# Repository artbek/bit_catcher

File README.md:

Bit Catcher (Mini Game Console)
===============================

Video: https://youtu.be/HpCyLKLNJE4

<br />

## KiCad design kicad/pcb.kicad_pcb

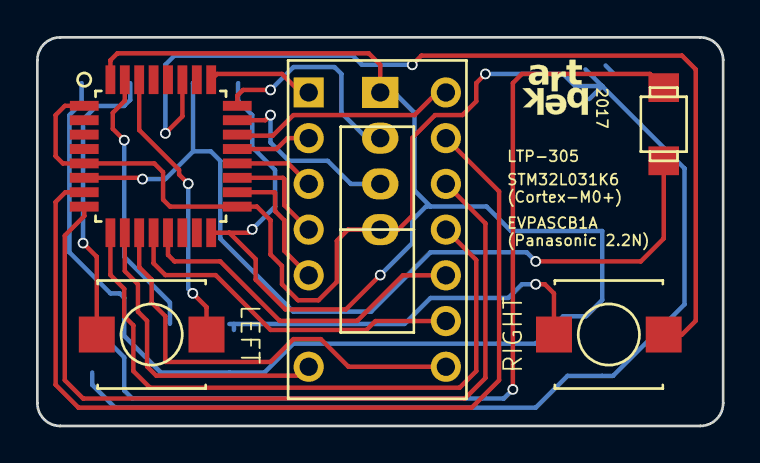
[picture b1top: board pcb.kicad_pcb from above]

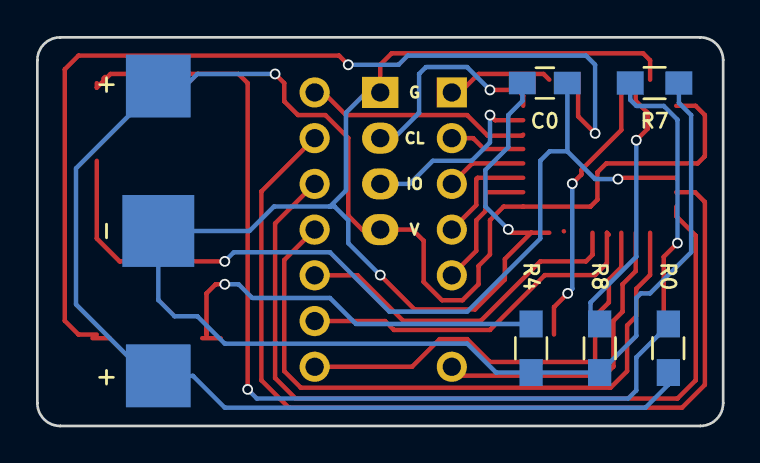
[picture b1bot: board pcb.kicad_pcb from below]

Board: 2 copper layers, 38.1 x 21.6 mm, 12 parts (6 on the bottom side), 24 nets.

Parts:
BT0: Battery_Cell; BatteryHolder_1220
BTN4: RIGHT; SW_PANASONIC
BTN7: LEFT; SW_PANASONIC
C0: 100nF; C_0805_HandSoldering
J0: Conn_01x04; SWD_PROGRAMMING_HEADER
R0, R4, R7, R8: 2k; R_0805_HandSoldering
S0: 5x7_DISPLAY_LTP-305; 2x7_dot_matrix
SW0: ON_OFF; SW_OMRON_SMALL
U0: STM32L031x4/6; TQFP-32_7x7mm_Pitch0.8mm

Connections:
+3V3: BT0.1, J0.4, R0.1, U0.1, U0.5, U0.17
GND: BT0.2, C0.2, J0.1, R4.1, R7.1, R8.1, U0.16, U0.32
unnamed: C0.1, SW0.1, U0.6
unnamed: J0.2, U0.24
unnamed: J0.3, U0.23
unnamed: R0.2, SW0.2
unnamed: BTN4.1, R4.2
unnamed: BTN7.2, R7.2
unnamed: R8.2, U0.31
unnamed: S0.1C, U0.25
unnamed: S0.2, U0.21
unnamed: S0.3, U0.20
unnamed: S0.4, U0.19
unnamed: S0.5C, U0.18
unnamed: S0.7, U0.10
unnamed: S0.8C, U0.11
unnamed: S0.9, U0.12
unnamed: S0.10, U0.13
unnamed: S0.11, U0.9
unnamed: S0.12, U0.8
unnamed: S0.13C, U0.7
unnamed: S0.14C, U0.22
unnamed: BTN4.2, U0.27
unnamed: BTN7.1, U0.30

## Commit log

2017-08-28 Initial.
2017-09-03 dflsj
2017-09-10 Bouncing ball.
2017-09-17 Refactored into header files. Bits instead of arrays.
2017-09-19 Working scoring and horizontal scrolling.
2017-10-09 Code initial.
2017-10-14 KiCad initial.
2017-10-14 Firmware directory.
2017-10-15 Getting there.
2017-10-16 PCB ready.
2017-10-19 Gradient.
2017-10-22 Horiontal scrolling.
2017-10-29 Working TIM21 and EEPROM.
2017-10-31 Tidy up, nicer EEPROM script, 3rd stage.
2017-11-02 Working game. HSI16. Fade in/out transitions.
2017-11-03 More randomness. Slower clock. Naming.
2017-11-04 Intro poster. Hi score. Smoother fading.
2017-11-05 Tweak constants. Readme + images.
2017-11-07 Update README.md (video).
2020-02-24 Update README (fix broken video link).
